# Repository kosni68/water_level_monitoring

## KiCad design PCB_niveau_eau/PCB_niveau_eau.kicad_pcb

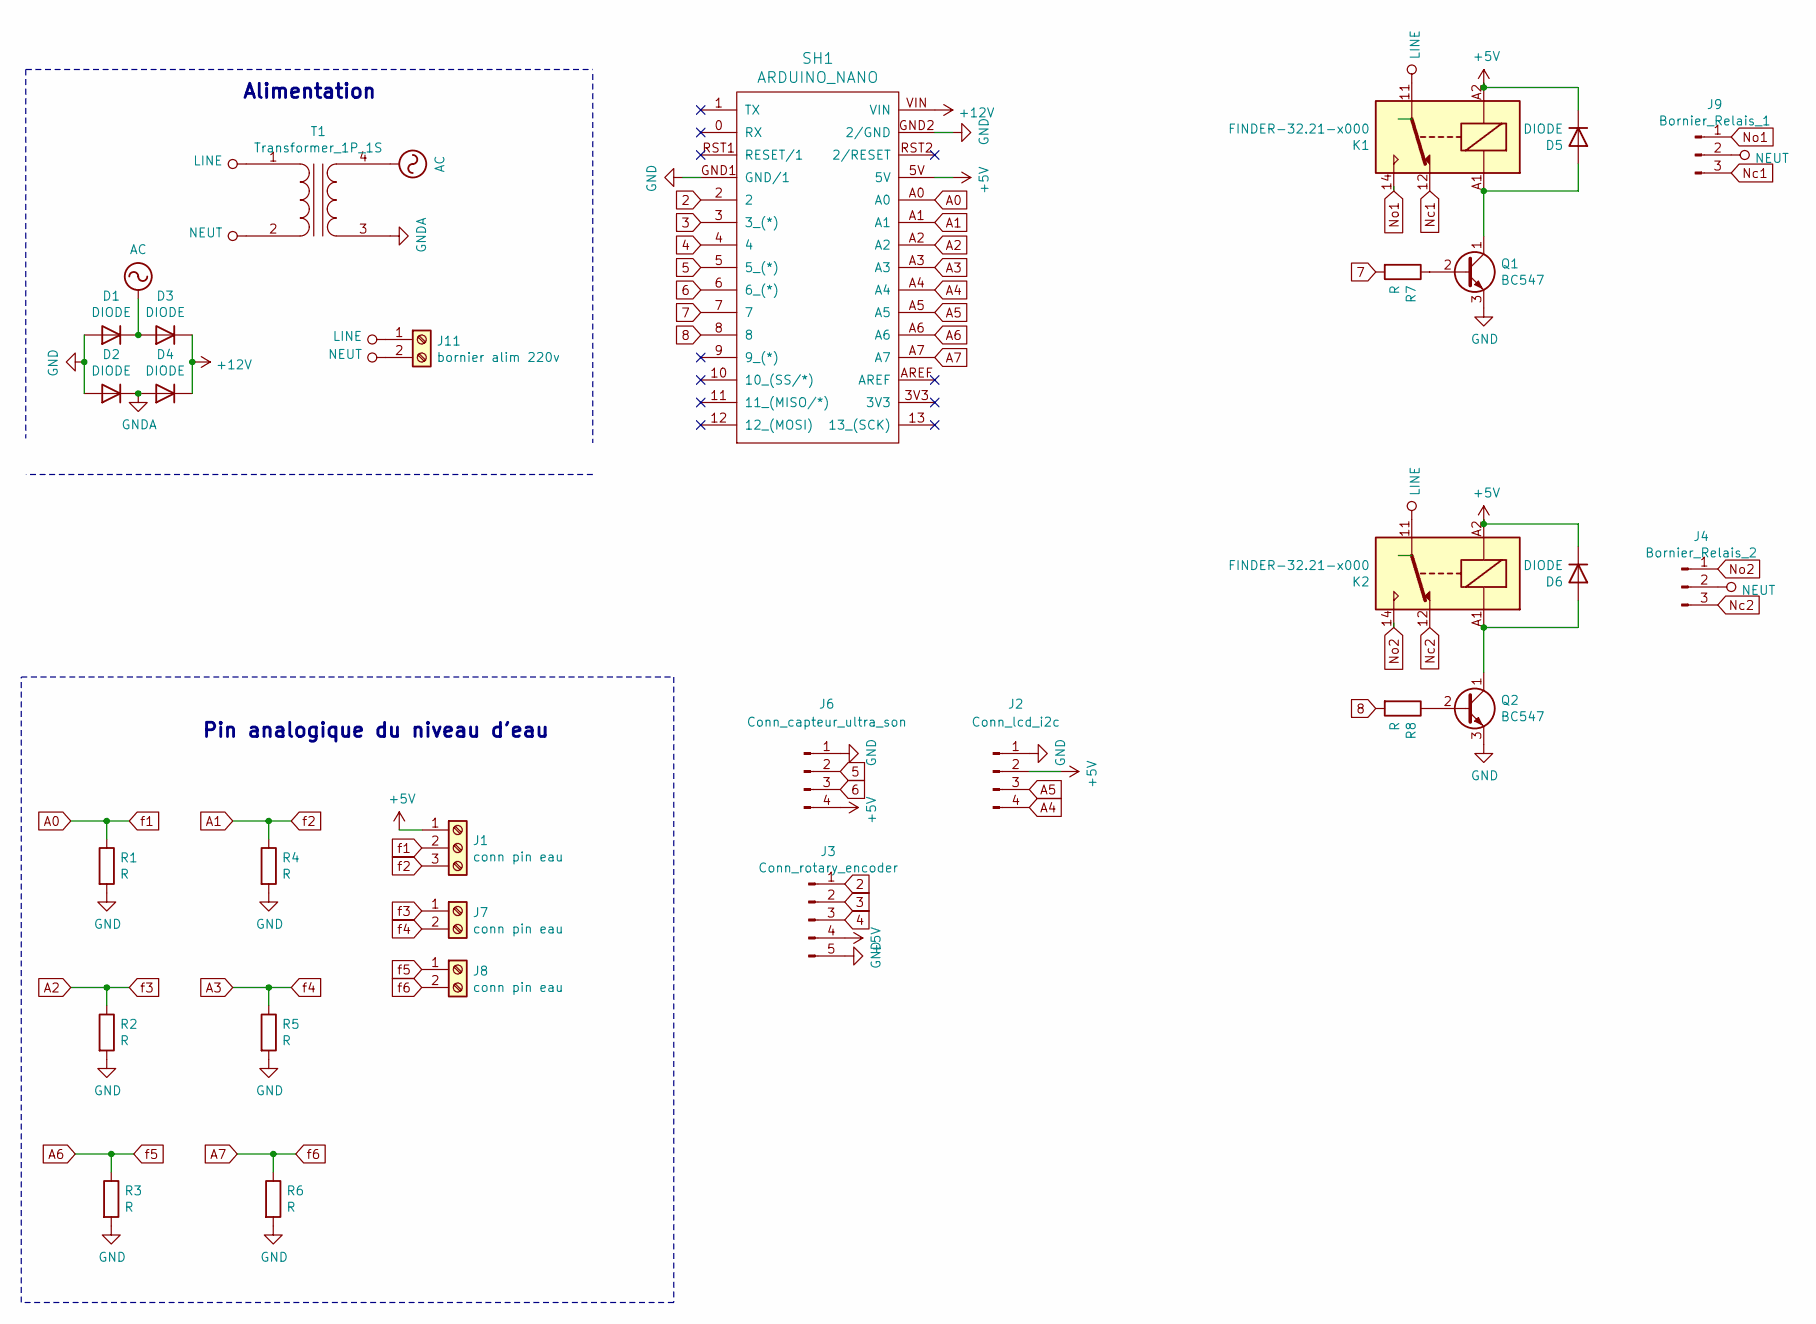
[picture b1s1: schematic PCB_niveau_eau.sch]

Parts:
D1, D2, D3, D4, D5, D6: DIODE; R_L6.3mm_D2.5mm_P10.16mm_Horizontal_PCB
J1: conn pin eau; Bornier_3p_5mm_chinois
J2: Conn_lcd_i2c; JST_XH_B4B-XH-A_1x04_P2.50mm_Vertical
J3: Conn_rotary_encoder; PinHeader_1x05_P2.54mm_Vertical_PCB
J4: Bornier_Relais_2; Bornier_3p_5mm_chinois
J6: Conn_capteur_ultra_son; JST_XH_B4B-XH-A_1x04_P2.50mm_Vertical
J7, J8: conn pin eau; Bornier_2p_5mm_chinois
J9: Bornier_Relais_1; Bornier_3p_5mm_chinois
J11: bornier alim 220v; Bornier_2p_5mm_chinois
K1, K2: FINDER-32.21-x000; Relay_SPDT_Finder_36.11
Q1, Q2: BC547; TO-92_Inline
R1, R2, R3, R4, R5, R6, R7, R8: R; R_1206_3216Metric_Pad1.42x1.75mm_HandSolder
SH1: ARDUINO_NANO; ARDUINO_NANO_2_CONTOUR
T1: Transformer_1P_1S; Transformer_Breve_TEZ-35x42

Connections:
2: J3.1, SH1.2
3: J3.2, SH1.3 (3_(*))
4: J3.3, SH1.4
5: J6.2, SH1.5 (5_(*))
6: J6.3, SH1.6 (6_(*))
7: R7.2, SH1.7
8: R8.2, SH1.8
+5V: D5.2 (K), D6.2 (K), J1.1, J2.2, J3.4, J6.4, K1.A2, K2.A2, SH1.5V
+12V: D3.2 (K), D4.2 (K), SH1.VIN
A0: J1.2, R1.1, SH1.A0
A1: J1.3, R4.1, SH1.A1
A2: J7.1, R2.1, SH1.A2
A3: J7.2, R5.1, SH1.A3
A4: J2.4, SH1.A4
A5: J2.3, SH1.A5
A6: J8.1, R3.1, SH1.A6
A7: J8.2, R6.1, SH1.A7
AC: D1.2 (K), D3.1 (A), T1.4 (SB)
GND: D1.1 (A), D2.1 (A), J2.1, J3.5, J6.1, Q1.3 (E), Q2.3 (E), R1.2, R2.2, R3.2, R4.2, R5.2, R6.2, SH1.GND1 (GND/1), SH1.GND2 (2/GND)
GNDA: D2.2 (K), D4.1 (A), T1.3 (SA)
LINE: J11.1, K1.11, K2.11, T1.1 (AA)
NEUT: J4.2, J9.2, J11.2, T1.2 (AB)
Nc1: J9.3, K1.12
Nc2: J4.3, K2.12
unnamed: D5.1 (A), K1.A1, Q1.1 (C)
unnamed: D6.1 (A), K2.A1, Q2.1 (C)
unnamed: Q1.2 (B), R7.1
unnamed: Q2.2 (B), R8.1
No1: J9.1, K1.14
No2: J4.1, K2.14

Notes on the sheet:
Alimentation
Pin analogique du niveau d'eau

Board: 2 copper layers, 29 parts (0 on the bottom side), 30 nets, no tracks yet.
